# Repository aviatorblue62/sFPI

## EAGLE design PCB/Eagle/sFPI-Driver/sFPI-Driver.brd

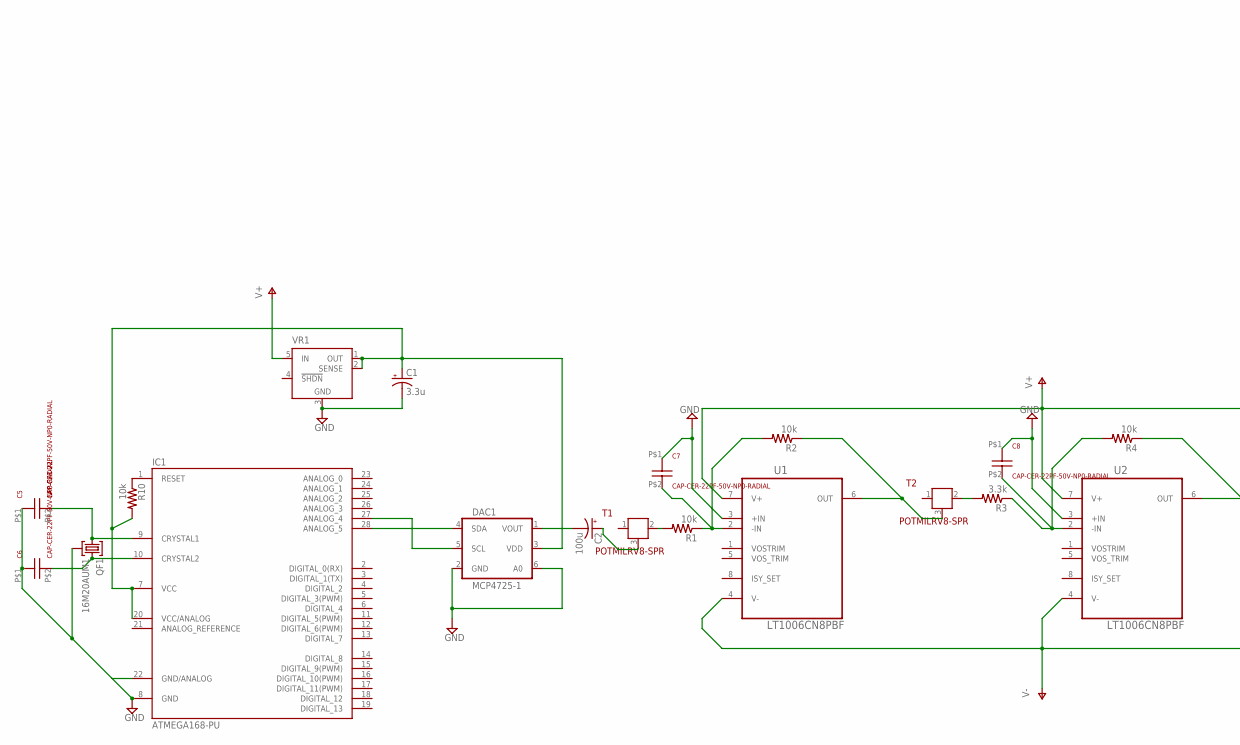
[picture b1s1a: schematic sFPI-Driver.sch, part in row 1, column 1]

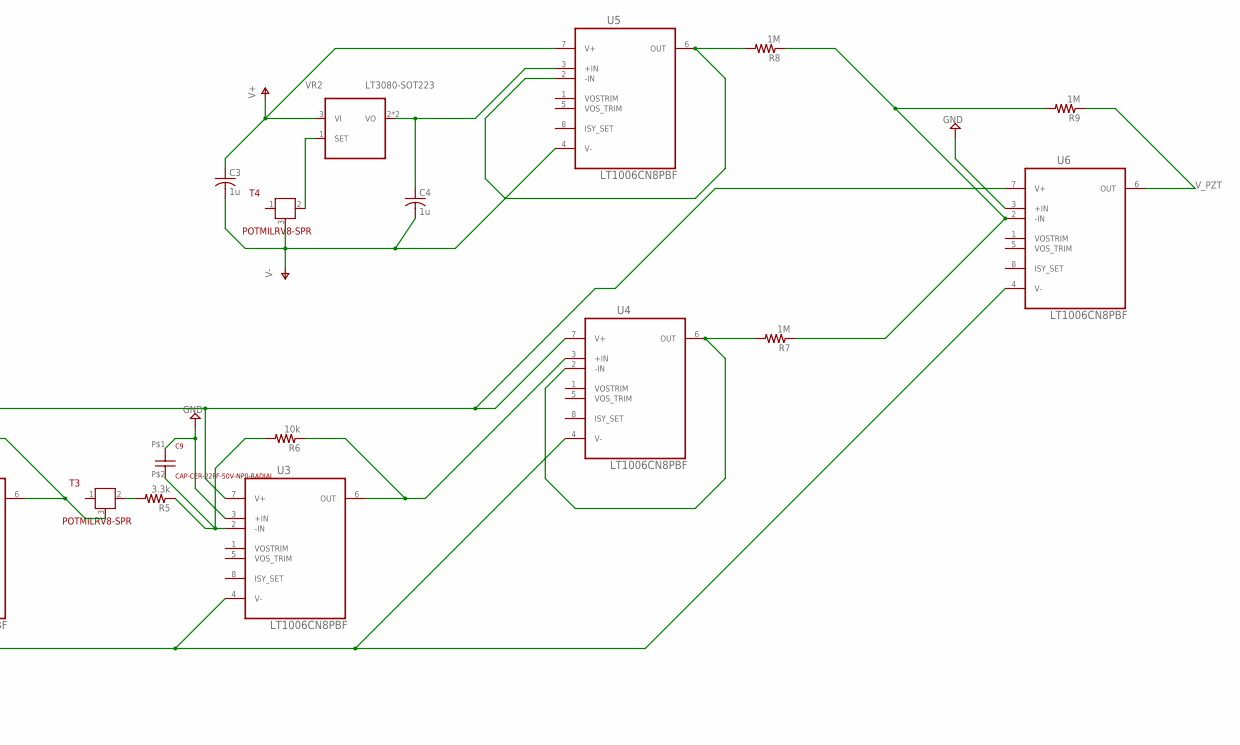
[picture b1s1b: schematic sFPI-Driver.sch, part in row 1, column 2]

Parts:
C1: 3.3u; CT3216
C2: 100u; PANASONIC_C
C3, C4: 1u; C050-030X075
C5, C6, C7, C8, C9: CAP-CER-22PF-50V-NP0-RADIAL; FG28
DAC1: MCP4725-1; SOT23-6
IC1: ATMEGA168-PU; DIL28-3
QF1: 16M20AUM1; UM1
R1, R2, R4, R6, R10: 10k; M1206
R3, R5: 3.3k; M1206
R7, R8, R9: 1M; M1206
T1, T2, T3, T4: POTMILRV8-SPR; SPR
U1, U2, U3, U4, U5, U6: LT1006CN8PBF; DIP254P762X393-8
VR1: LT1129CQ-5; Q5-DD
VR2: LT3080-SOT223; SOT223

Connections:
GND: C1.-, C5.P$1 (1), C6.P$1 (1), C7.P$1 (1), C8.P$1 (1), C9.P$1 (1), DAC1.2 (GND), DAC1.6 (A0), IC1.8 (GND), IC1.22 (GND/ANALOG), QF1.2, U1.3 (+IN), U2.3 (+IN), U3.3 (+IN), U6.3 (+IN), VR1.3 (GND)
unnamed: C5.P$2 (2), IC1.9 (CRYSTAL1), QF1.1
unnamed: C6.P$2 (2), IC1.10 (CRYSTAL2), QF1.3
unnamed: IC1.1 (RESET), R10.1
unnamed: C1.+, DAC1.3 (VDD), IC1.7 (VCC), IC1.20 (VCC/ANALOG), R10.2, VR1.1 (OUT), VR1.2 (SENSE)
unnamed: R2.1, T2.3, T3.3, U1.6 (OUT)
unnamed: C7.P$2 (2), C8.P$2 (2), R1.1, R2.2, R3.1, R4.2, U1.2 (-IN)
unnamed: DAC1.5 (SCL), IC1.27 (ANALOG_4)
unnamed: DAC1.4 (SDA), IC1.28 (ANALOG_5)
unnamed: C2.+, T1.3
unnamed: R1.2, T1.2
unnamed: C2.-, DAC1.1 (VOUT)
unnamed: R3.2, T2.2
unnamed: R5.2, T3.2
unnamed: C9.P$2 (2), R5.1, R6.2, U3.2 (-IN)
unnamed: R6.1, U3.6 (OUT), U4.3 (+IN)
unnamed: R8.2, U5.2 (-IN), U5.6 (OUT)
unnamed: R7.1, R8.1, R9.2, U6.2 (-IN)
unnamed: C4.1, U5.3 (+IN), VR2.2 (VO), VR2.4 (VO)
unnamed: T4.2, VR2.1 (SET)
unnamed: R7.2, U4.2 (-IN), U4.6 (OUT)
V+: C3.1, U1.7 (V+), U2.7 (V+), U3.7 (V+), U4.7 (V+), U5.7 (V+), U6.7 (V+), VR1.5 (IN), VR2.3 (VI)
V-: C3.2, C4.2, T4.3, U2.4 (V-), U3.4 (V-), U4.4 (V-), U5.4 (V-), U6.4 (V-)
V_PZT: R9.1, U6.6 (OUT)

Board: 2 copper layers, 34 parts (0 on the bottom side), 24 nets, no tracks yet.

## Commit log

2016-01-16 First commit on MacBook Pro
2016-01-16 Electrical Schematics Added
2016-01-17 Added commit repo bash script
2016-01-17 "Added same-line entry for message"
2016-01-20 Added LT1006 OpAmp and 1Meg Resistors
2016-01-20 Added 100uF CAP - 1MEG RES - BETTER DAC_SIGNAL
2016-01-20 Eagle Layout UPDATE - LTSPICE UPDATE
2016-01-20 Added Parts List
2016-01-20 Added OPAMPS in EAGLE SCH
2016-01-20 Added Thesis Paper
2016-01-22 sFPI - Rev 1
2016-01-22 Moved Datasheets
2016-01-30 sFPI - Rev 2
2016-01-30 sFPI - Rev 3
2016-01-30 Further analysis of driver frequency spectrum
2016-02-05 sFPI - Updated Parts List - Updated LTSpice Models and Scripts
2016-03-18 Final Revision
2016-03-18 ReEdited Paper with final changes
2016-03-18 Turing it in now
